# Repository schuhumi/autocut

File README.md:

autoCut
=======

autoCut is an automatic lawn mower robot. It features:
 - Four weel drive with kink steering
 - Motorized mowing height leveling
 - Two 85 watt mowing motors, each equipped with two very sharp blades, able to snap back on hard obstacles
 - On the fly interchangeable LiPo-battery with voltage monitoring
 - Wifi network connection for web interface which includes gamepad remote control
 - Raspberry Pi as its main computer and head of the microcontroller i2c-network

progress
========

What it can do already:
-----------------------
 - [drive system] works pretty much brilliant
 - [power supply] Measures individual cell voltages and rings an audible alarm in case of undervoltage or improper connected battery. Handles battery changes without losing power for the control system
 - [main module] Raspberry works quite well with ArchLinux ARM and provides a webinterface on the network. Will be replaced by Cubieboard 2 since RasPi has hardware I2C issues
 - [mowing module] Runs the mowing motors with a reasonably decent rpm regulation algorithm. Electrical mowing height adjustment through web interface is implemented.

What it can't do yet:
---------------------
 - [power supply] Measure the current as well as the total battery voltage
 - [general] No environmental sensoring for automatic movement yet, so manual control is needed

Things to improve:
------------------
 - [power supply] design a proper pcb (its on a prototyping board so far)
 - [mowing module] Change FETs for ones with lower heat dissipation and enhance the rpm regulation algorithm

Preserved for the future:
-------------------------
 - Build an automatic battery changing and charging station

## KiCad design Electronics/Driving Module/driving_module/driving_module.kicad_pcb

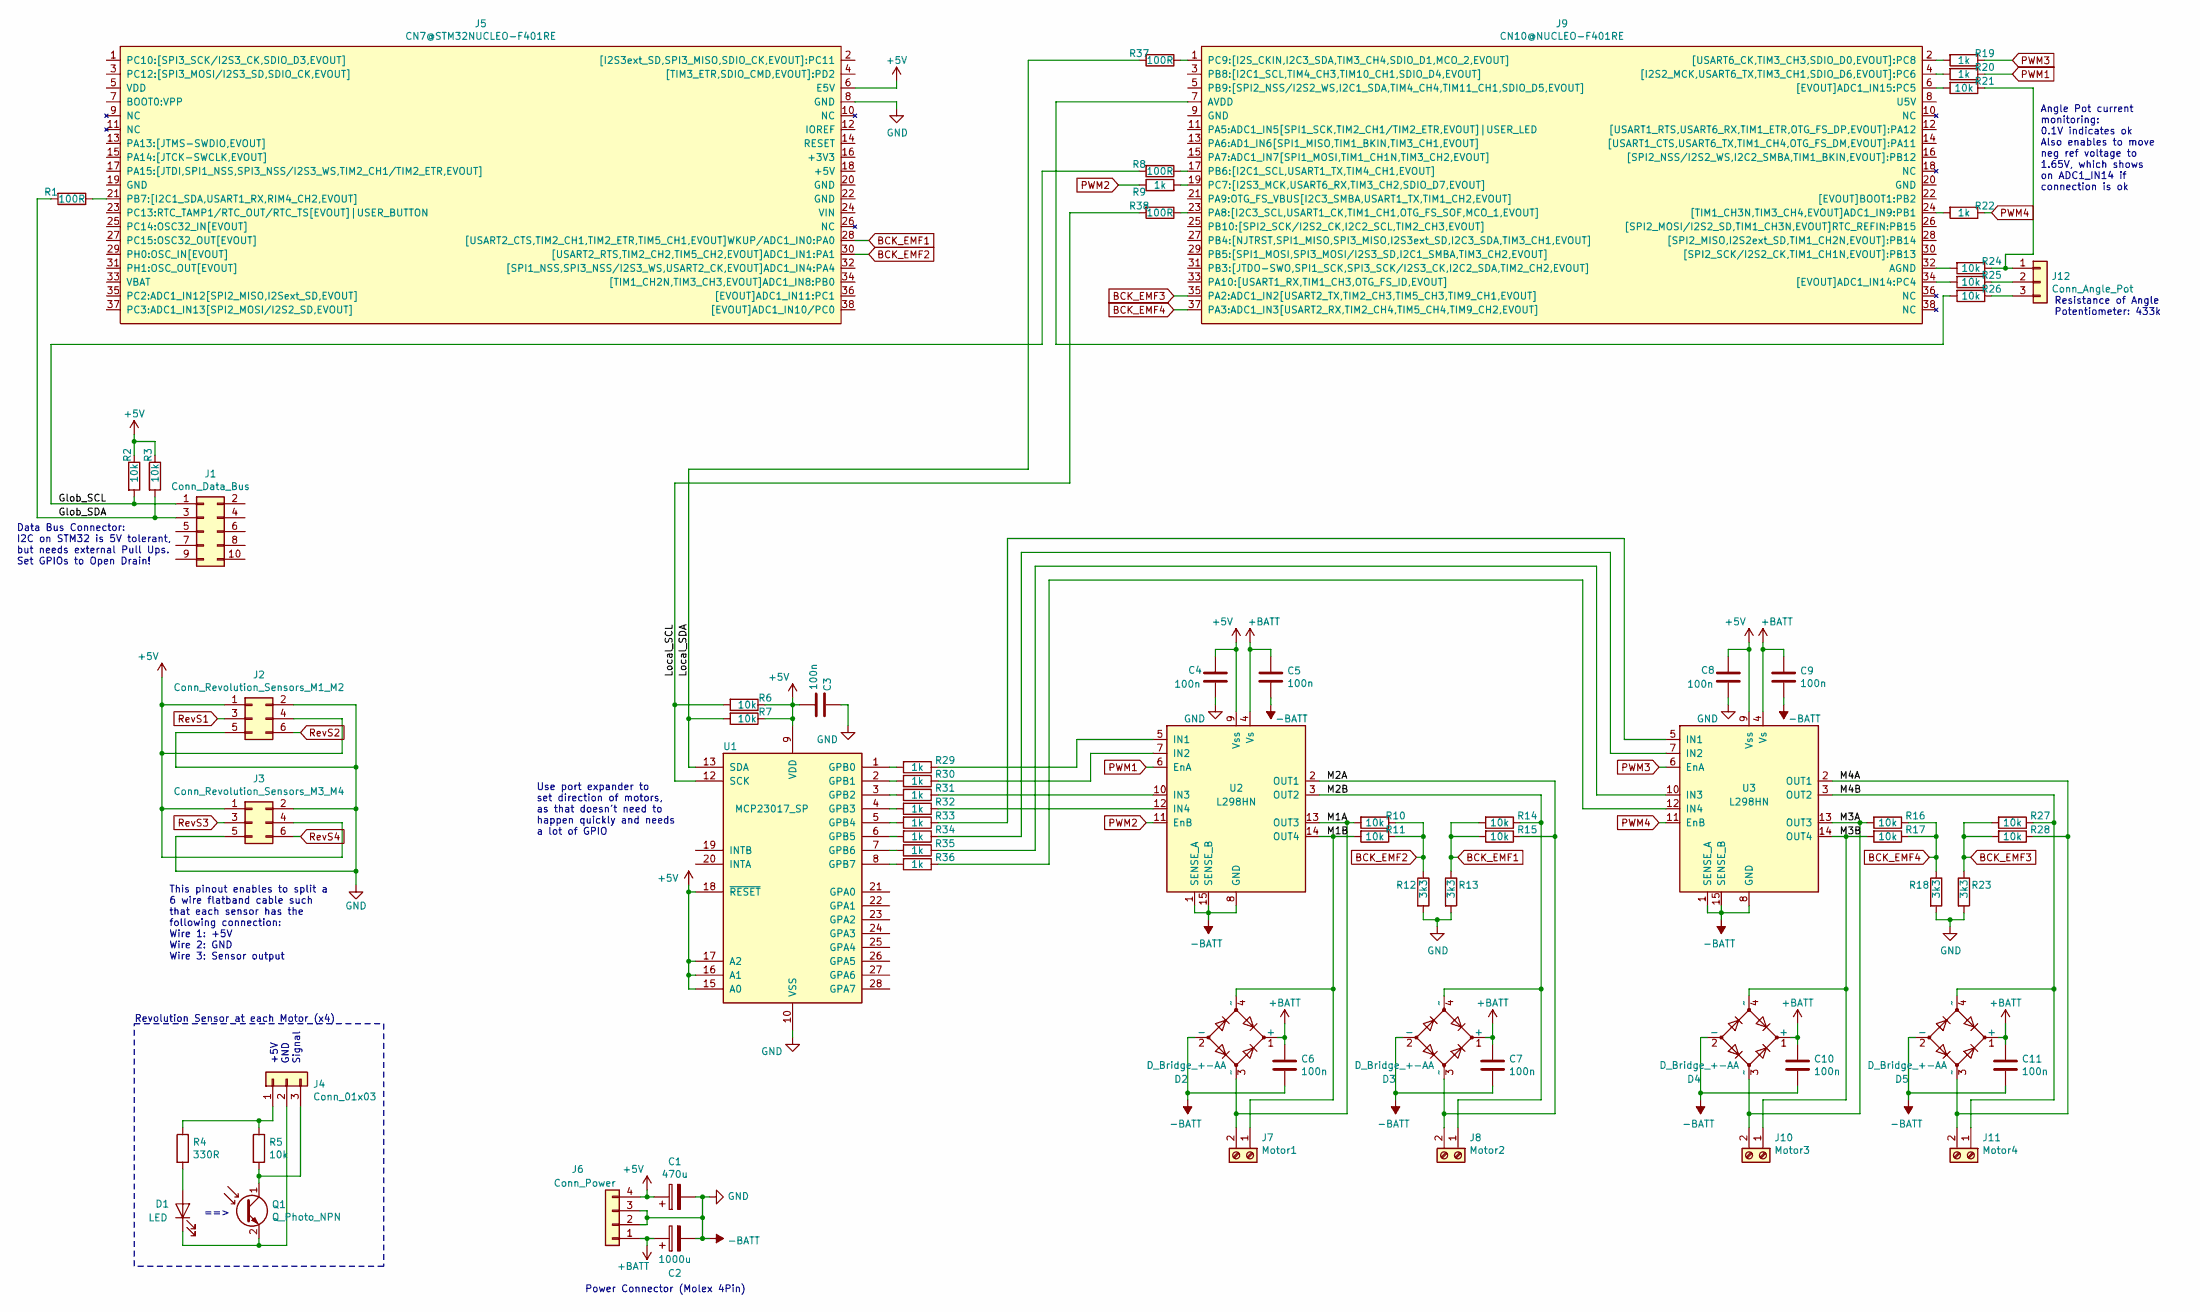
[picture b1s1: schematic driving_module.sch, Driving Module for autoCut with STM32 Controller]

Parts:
C1: 470u; CP_Radial_D8.0mm_P5.00mm
C2: 1000u; CP_Radial_D12.5mm_P5.00mm
C3, C4, C5, C6, C7, C8, C9, C10, C11: 100n; C_0805_2012Metric
D1: LED; LED_D3.0mm_Clear
D2, D3, D4, D5: D_Bridge_+-AA; Diode_Bridge_Diotec_SO-DIL-Slim
J1: Conn_Data_Bus; IDC-Header_2x05_P2.54mm_Vertical
J2: Conn_Revolution_Sensors_M1_M2; IDC-Header_2x03_P2.54mm_Vertical
J3: Conn_Revolution_Sensors_M3_M4; IDC-Header_2x03_P2.54mm_Vertical
J4: Conn_01x03; PinHeader_1x03_P2.54mm_Vertical
J5: CN7@STM32NUCLEO-F401RE; PinSocket_2x19_P2.54mm_Vertical
J6: Conn_Power; xess-MOLEX-8981-04P
J7: Motor1; TerminalBlock_bornier-2_P5.08mm
J8: Motor2; TerminalBlock_bornier-2_P5.08mm
J9: CN10@NUCLEO-F401RE; PinSocket_2x19_P2.54mm_Vertical
J10: Motor3; TerminalBlock_bornier-2_P5.08mm
J11: Motor4; TerminalBlock_bornier-2_P5.08mm
J12: Conn_Angle_Pot; PinHeader_1x03_P2.54mm_Vertical
Q1: Q_Photo_NPN; LED_D3.0mm_Clear
R1, R8, R37, R38: 100R; R_0805_2012Metric
R2, R3, R5, R6, R7, R10, R11, R14, R15, R16, R17, R21, R24, R25, R26, R27, R28: 10k; R_0805_2012Metric
R4: 330R; R_0805_2012Metric
R9, R19, R20, R22, R29, R30, R31, R32, R33, R34, R35, R36: 1k; R_0805_2012Metric
R12, R13, R18, R23: 3k3; R_Axial_DIN0207_L6.3mm_D2.5mm_P7.62mm_Horizontal
U1: MCP23017_SP; DIP-28_W7.62mm
U2, U3: L298HN; TO-220-15_P2.54x2.54mm_StaggerOdd_Lead4.58mm_Vertical_bent_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

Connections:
+5V: C1.1, C3.2, C4.1, C8.1, J2.1, J2.4, J3.1, J3.4, J5.6 (E5V), J6.4, R2.1, R3.1, R6.1, R7.1, U1.9 (VDD), U1.15 (A0), U1.16 (A1), U1.17 (A2), U1.18 (~RESET~), U2.9 (Vss), U3.9 (Vss)
+BATT: C2.1, C5.1, C6.1, C7.1, C9.1, C10.1, C11.1, D2.1 (+), D3.1 (+), D4.1 (+), D5.1 (+), J6.1, U2.4 (Vs), U3.4 (Vs)
-BATT: C1.2, C2.2, C3.1, C4.2, C5.2, C6.2, C7.2, C8.2, C9.2, C10.2, C11.2, D2.2 (-), D3.2 (-), D4.2 (-), D5.2 (-), J2.2, J2.5, J3.2, J3.5, J5.8 (GND), J6.2, J6.3, R12.2, R13.2, R18.2, R23.2, U1.10 (VSS), U2.1 (SENSE_A), U2.8 (GND), U2.15 (SENSE_B), U3.1 (SENSE_A), U3.8 (GND), U3.15 (SENSE_B)
/Glob_SCL: J1.1, R2.2, R8.2
/Glob_SDA: J1.3, R1.2, R3.2
/Local_SCL: R6.2, R38.2, U1.12 (SCK)
/Local_SDA: R7.2, R37.2, U1.13 (SDA)
/M1A: D2.3 (~~), J7.2, R10.2, U2.13 (OUT3)
/M1B: D2.4 (~~), J7.1, R11.2, U2.14 (OUT4)
/M2A: D3.3 (~~), J8.2, R15.1, U2.2 (OUT1)
/M2B: D3.4 (~~), J8.1, R14.1, U2.3 (OUT2)
/M3A: D4.3 (~~), J10.2, R16.2, U3.13 (OUT3)
/M3B: D4.4 (~~), J10.1, R17.2, U3.14 (OUT4)
/M4A: D5.3 (~~), J11.2, R28.1, U3.2 (OUT1)
/M4B: D5.4 (~~), J11.1, R27.1, U3.3 (OUT2)
BCK_EMF1: J5.28 ([USART2_CTS,TIM2_CH1,TIM2_ETR,TIM5_CH1,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), R13.1, R14.2, R15.2
BCK_EMF2: J5.30 ([USART2_RTS,TIM2_CH2,TIM5_CH2,EVOUT]ADC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), R10.1, R11.1, R12.1
BCK_EMF3: J9.35 (PA2:ADC1_IN2[USART2_TX,TIM2_CH3,TIM5_CH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), R23.1, R27.2, R28.2
BCK_EMF4: J9.37 (PA3:ADC1_IN3[USART2_RX,TIM2_CH4,TIM5_CH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), R16.1, R17.1, R18.1
unnamed: D1.1 (K), J4.2, Q1.2 (E)
unnamed: D1.2 (A), R4.2
unnamed: J4.1, R4.1, R5.1
unnamed: J4.3, Q1.1 (C), R5.2
unnamed: J5.21 (PB7:[I2C1_SDA,USART1_RX,RIM4_CH2,EVOUT]), R1.1
unnamed: J9.1 (PC9:[I2S_CKIN,I2C3_SDA,TIM3_CH4,SDIO_D1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), R37.1
unnamed: J9.2 ([USART6_CK,TIM3_CH3,SDIO_D0,EVOUT]:PC8), R19.2
unnamed: J9.4 ([I2S2_MCK,USART6_TX,TIM3_CH1,SDIO_D6,EV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), R20.2
unnamed: J9.6 ([EVOUT]ADC1_IN15:PC5), R21.2
unnamed: J9.7 (AVDD), R26.2
unnamed: J9.17 (PB6:[I2C1_SCL,USART1_TX,TIM4_CH1,EVOUT]), R8.1
unnamed: J9.19 (PC7:[I2S3_MCK,USART6_RX,TIM3_CH2,SDIO_D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), R9.2
unnamed: J9.23 (PA8:[I2C3_SCL,USART1_CK,TIM1_CH1,OTG_FS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), R38.1
unnamed: J9.24 ([TIM1_CH3N,TIM3_CH4,EVOUT]ADC1_IN9:PB1), R22.2
unnamed: J9.32 (AGND), R24.2
unnamed: J9.34 ([EVOUT]ADC1_IN14:PC4), R25.2
unnamed: J12.1, R21.1, R24.1
unnamed: J12.2, R25.1
unnamed: J12.3, R26.1
unnamed: R29.1, U2.5 (IN1)
unnamed: R29.2, U1.1 (GPB0)
unnamed: R30.1, U2.7 (IN2)
unnamed: R30.2, U1.2 (GPB1)
unnamed: R31.1, U2.10 (IN3)
unnamed: R31.2, U1.3 (GPB2)
unnamed: R32.1, U2.12 (IN4)
unnamed: R32.2, U1.4 (GPB3)
unnamed: R33.1, U3.5 (IN1)
unnamed: R33.2, U1.5 (GPB4)
unnamed: R34.1, U3.7 (IN2)
unnamed: R34.2, U1.6 (GPB5)
unnamed: R35.1, U3.10 (IN3)
unnamed: R35.2, U1.7 (GPB6)
unnamed: R36.1, U3.12 (IN4)
unnamed: R36.2, U1.8 (GPB7)
PWM1: R20.1, U2.6 (EnA)
PWM2: R9.1, U2.11 (EnB)
PWM3: R19.1, U3.6 (EnA)
PWM4: R22.1, U3.11 (EnB)
RevS1: J2.3
RevS2: J2.6
RevS3: J3.3
RevS4: J3.6

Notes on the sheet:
Resistance of Angle Potentiometer: 433k
Angle Pot current monitoring: 0.1V indicates ok Also enables to move neg ref voltage to 1.65V, which shows on ADC1_IN14 if connection is ok
Data Bus Connector: I2C on STM32 is 5V tolerant, but needs external Pull Ups. Set GPIOs to Open Drain!
Use port expander to set direction of motors, as that doesn't need to happen quickly and needs a lot of GPIO
This pinout enables to split a 6 wire flatband cable such that each sensor has the following connection: Wire 1: +5V Wire 2: GND Wire 3: Sensor output
+5V GND Signal
==>
Revolution Sensor at each Motor (x4)
Power Connector (Molex 4Pin)

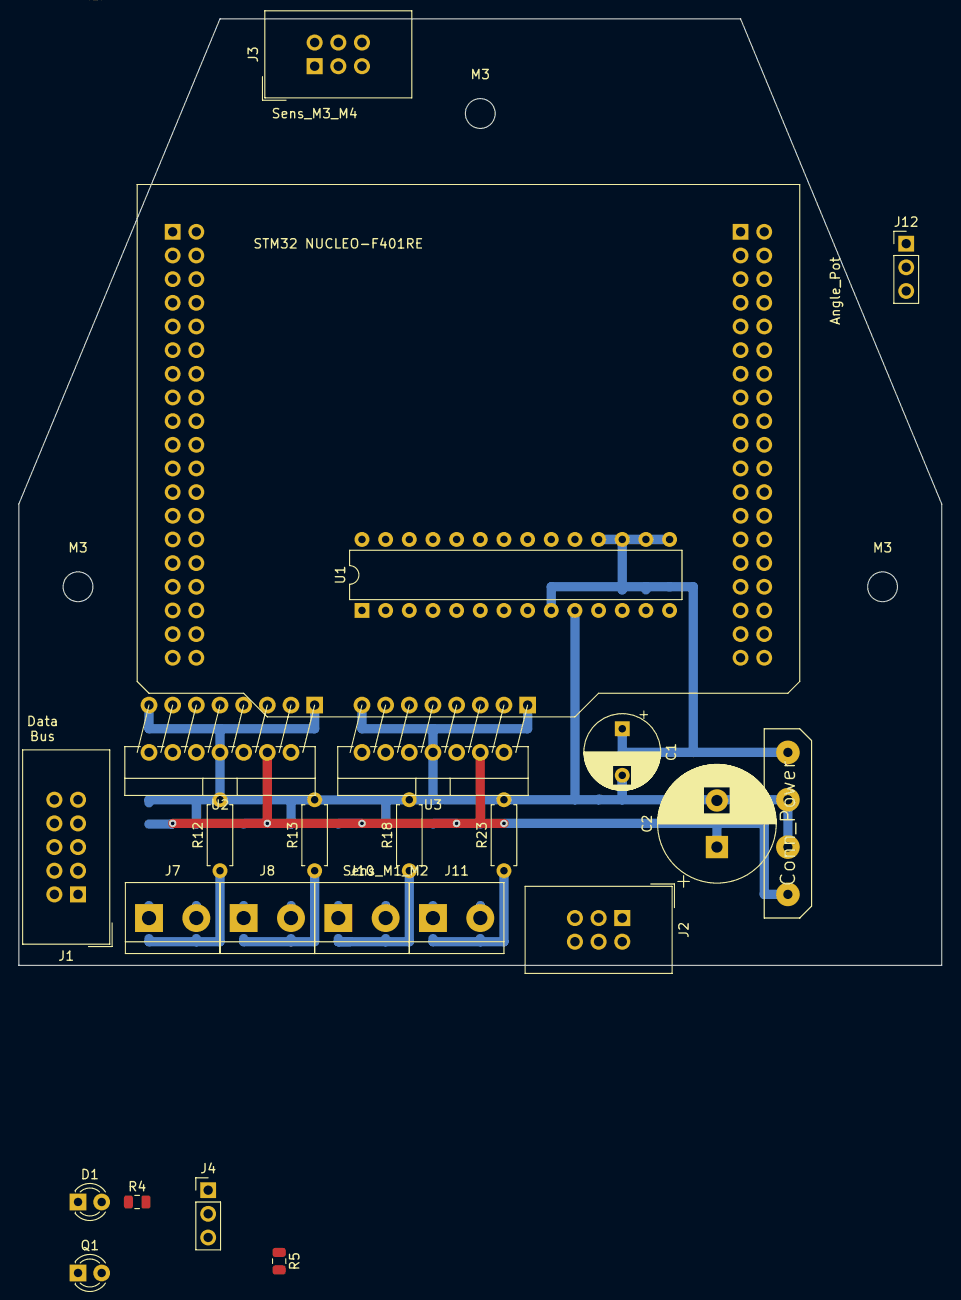
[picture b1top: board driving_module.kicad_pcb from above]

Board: 4 copper layers, 99.1 x 101.6 mm, 73 parts (0 on the bottom side), 58 nets.

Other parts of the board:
M3, M3#2, M3#3: MountingHole_3.2mm_M3

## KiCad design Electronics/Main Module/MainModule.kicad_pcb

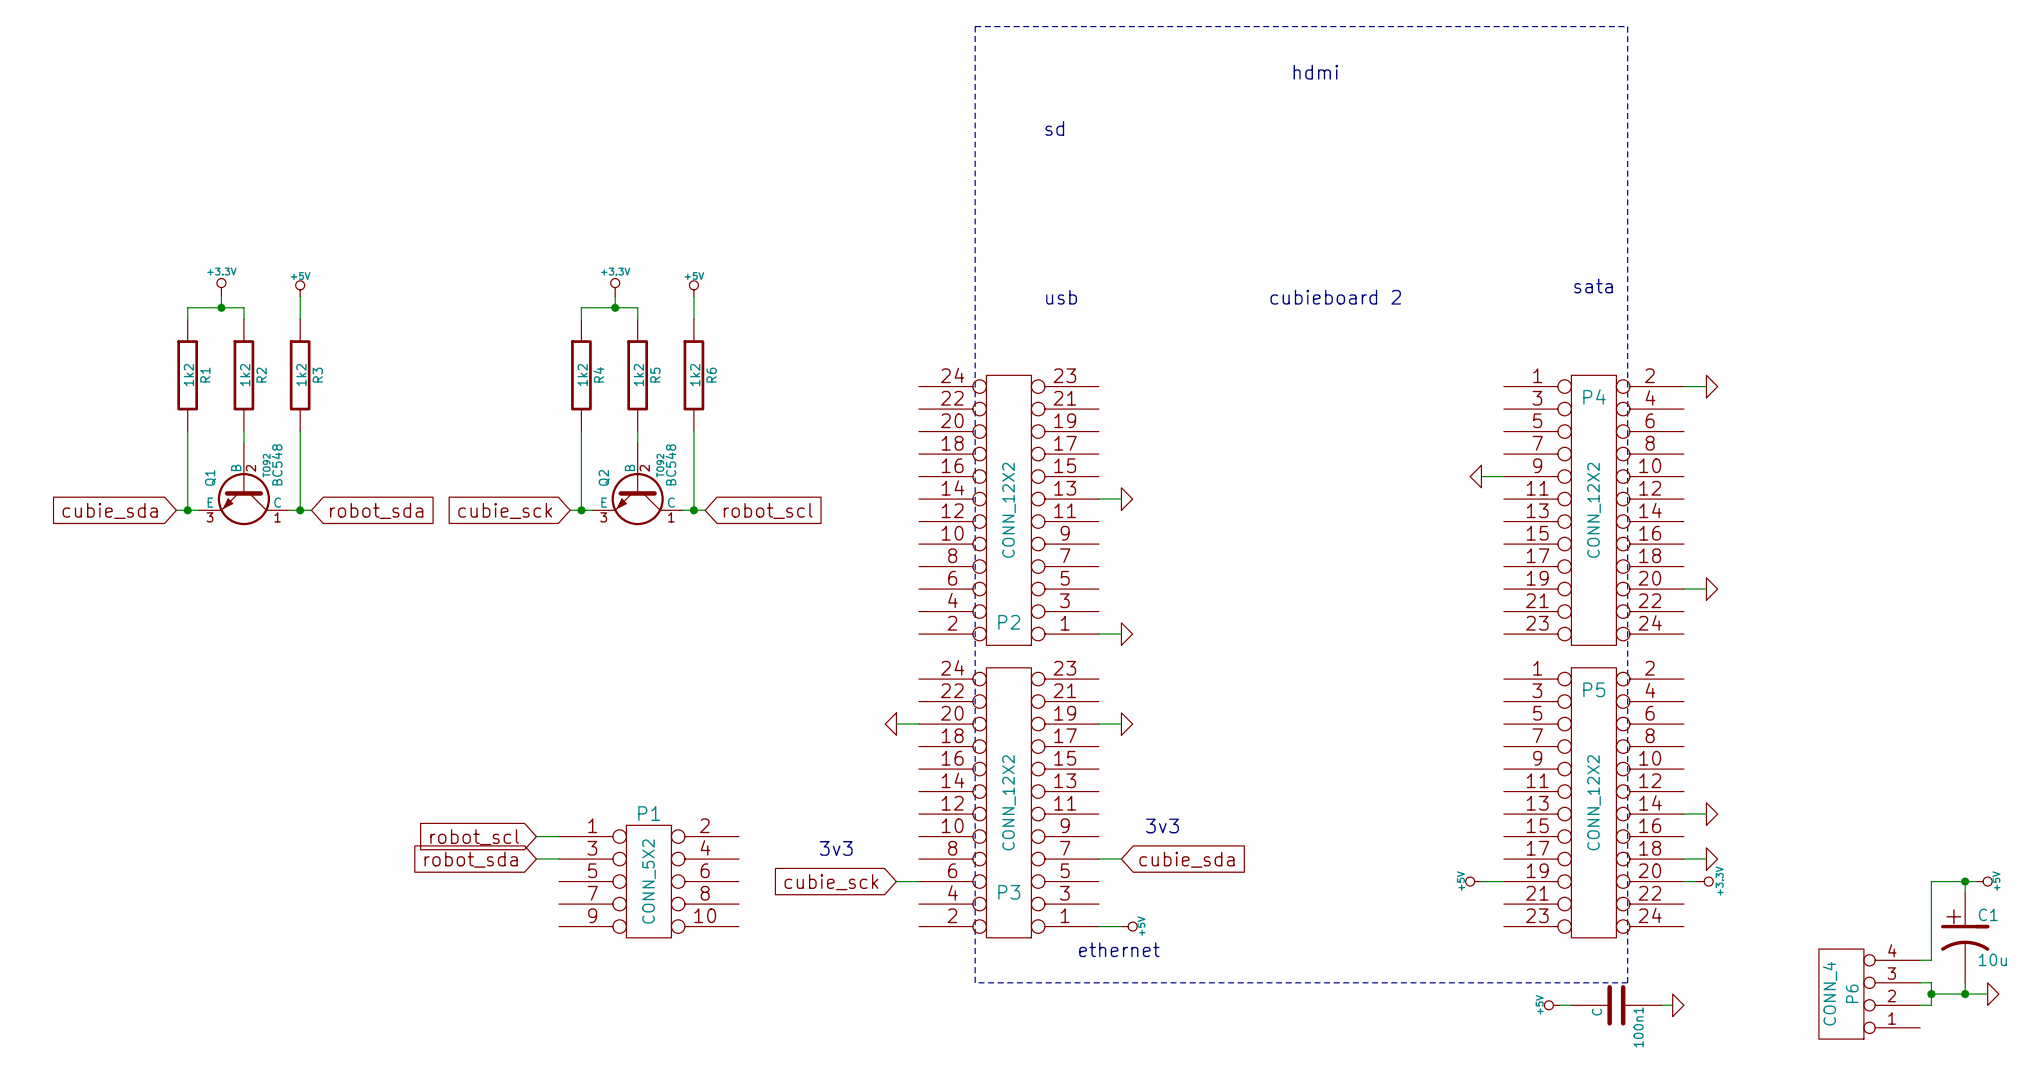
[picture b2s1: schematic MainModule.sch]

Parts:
100n1: C; SMD-0805
C1: 10u; Elko_vert_DM5_RM2-5
P1: CONN_5X2; VASCH5x2
P2, P3, P4, P5: CONN_12X2; SMD2mm_Header_12x2
P6: CONN_4; Molex
Q1, Q2: BC548; TO92
R1, R2, R3, R4, R5, R6: 1k2; R_0805

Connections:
+3.3V: P5.20, R1.1, R2.1, R4.1, R5.1
+5V: 100n1.2, C1.1, P3.1, P5.19, P6.4, R3.1, R6.1
GND: 100n1.1, C1.2, P2.1, P2.13, P3.19, P3.20, P4.2, P4.9, P4.20, P5.14, P5.18, P6.2, P6.3
unnamed: Q1.2 (B), R2.2
unnamed: Q2.2 (B), R5.2
cubie_sck: P3.6, Q2.3 (E), R4.2
cubie_sda: P3.7, Q1.3 (E), R1.2
robot_scl: P1.1, Q2.1 (C), R6.2
robot_sda: P1.3, Q1.1 (C), R3.2

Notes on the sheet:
cubieboard 2
sata
ethernet
usb
hdmi
3v3

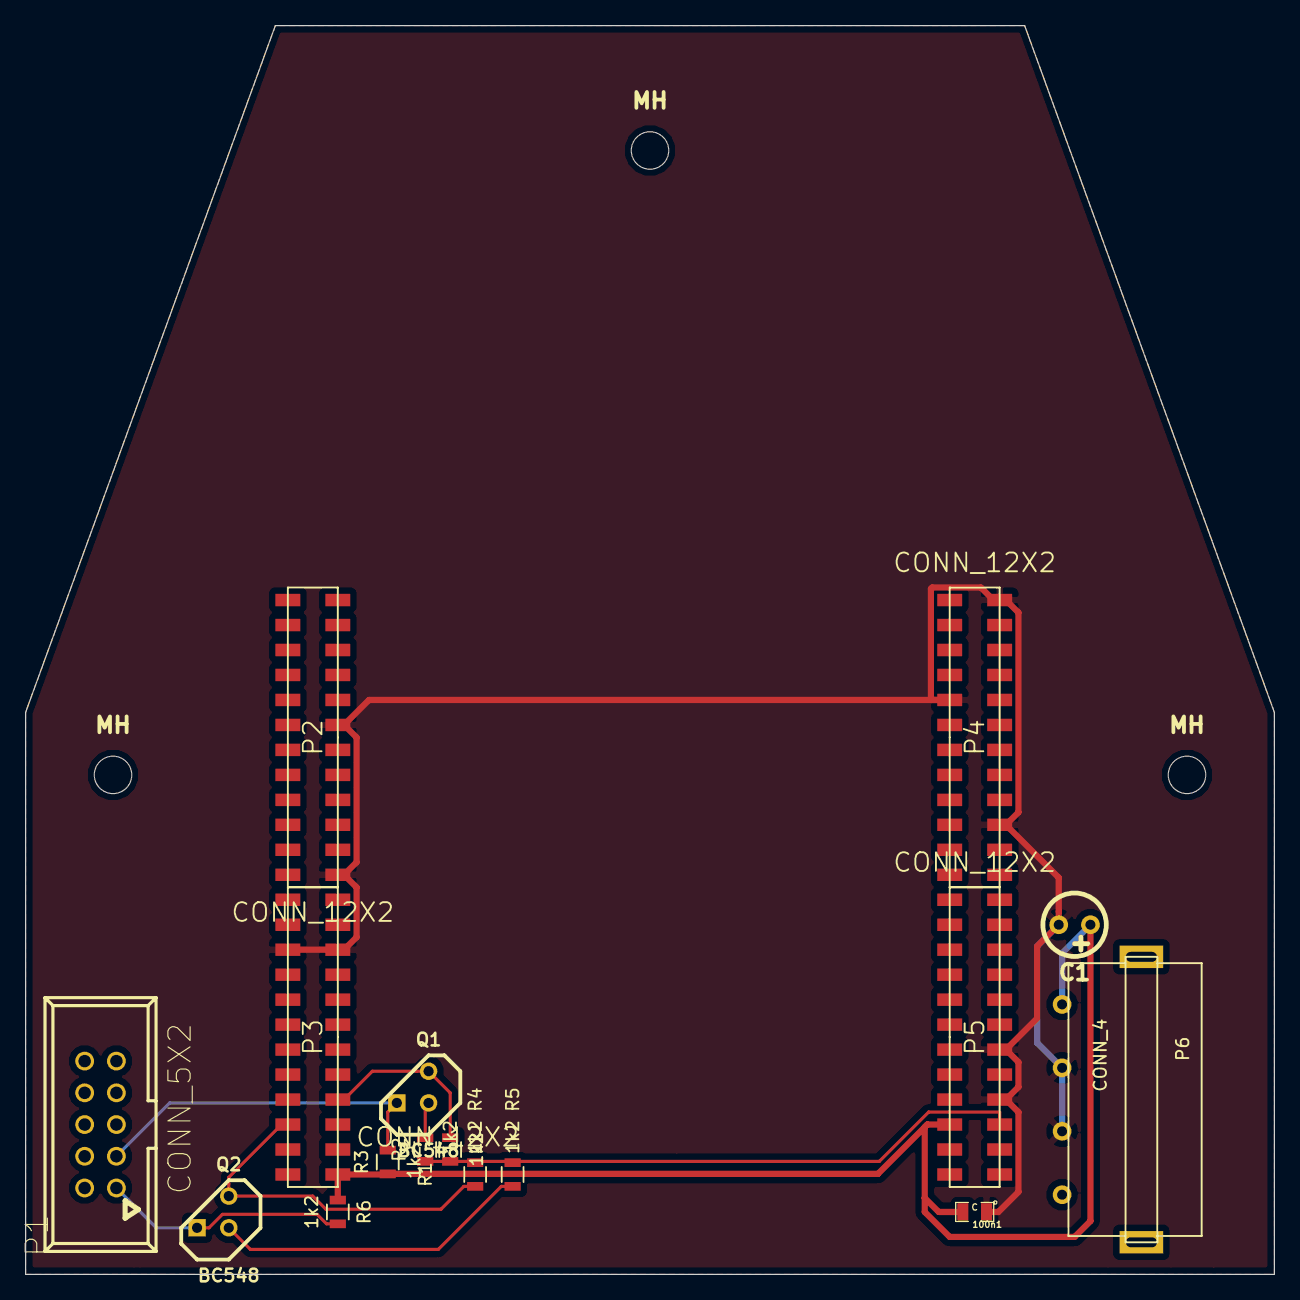
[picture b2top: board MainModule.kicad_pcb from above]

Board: 2 copper layers, 100.0 x 100.0 mm, 19 parts (0 on the bottom side), 9 nets.

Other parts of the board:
MH: MountingHole_3mm_RevA_Date21Jun2010; MountingHole_3mm
MH#2, MH#3: MountingHole_3mm_RevA_Date21Jun2010; MountingHole_3mm

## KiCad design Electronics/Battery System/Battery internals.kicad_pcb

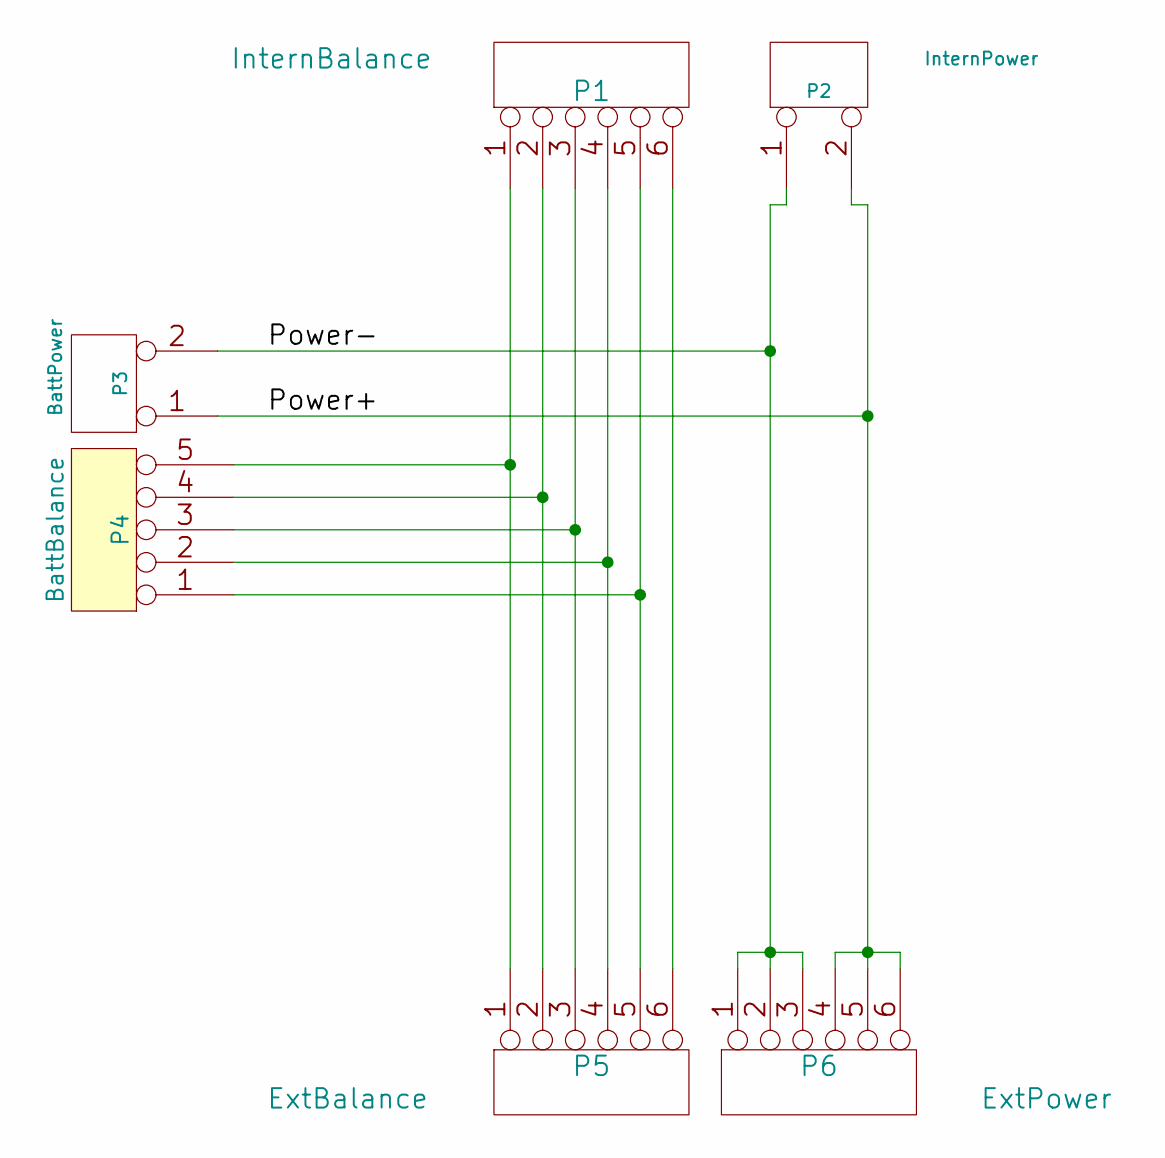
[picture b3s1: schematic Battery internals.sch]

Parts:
P1: InternBalance; Socket_Strip_Straight_1x06
P2: InternPower; PowerConnect_Handsolder
P3: BattPower; PowerConnect_Handsolder
P4: BattBalance; Pin_Header_Straight_1x05
P5: ExtBalance; Connector_MPX_6Pin
P6: ExtPower; Connector_MPX_6Pin

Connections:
/Power+: P2.2 (PM), P3.1, P6.4, P6.5, P6.6
/Power-: P2.1, P3.2 (PM), P6.1, P6.2, P6.3
unnamed: P1.1, P4.5, P5.1
unnamed: P1.2, P4.4, P5.2
unnamed: P1.3, P4.3, P5.3
unnamed: P1.4, P4.2, P5.4
unnamed: P1.5, P4.1, P5.5
unnamed: P1.6, P5.6

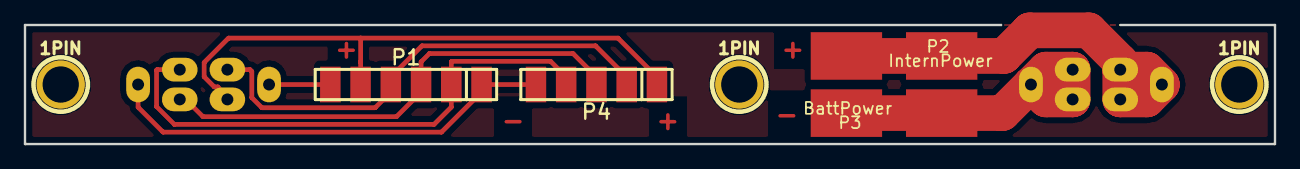
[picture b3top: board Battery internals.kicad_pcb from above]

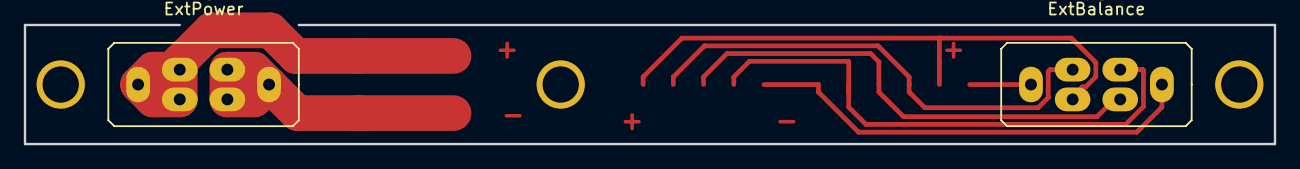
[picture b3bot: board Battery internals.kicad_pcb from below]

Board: 2 copper layers, 105.0 x 10.0 mm, 9 parts (2 on the bottom side), 8 nets.

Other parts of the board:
1PIN, 1PIN#2, 1PIN#3: P***; 1pin

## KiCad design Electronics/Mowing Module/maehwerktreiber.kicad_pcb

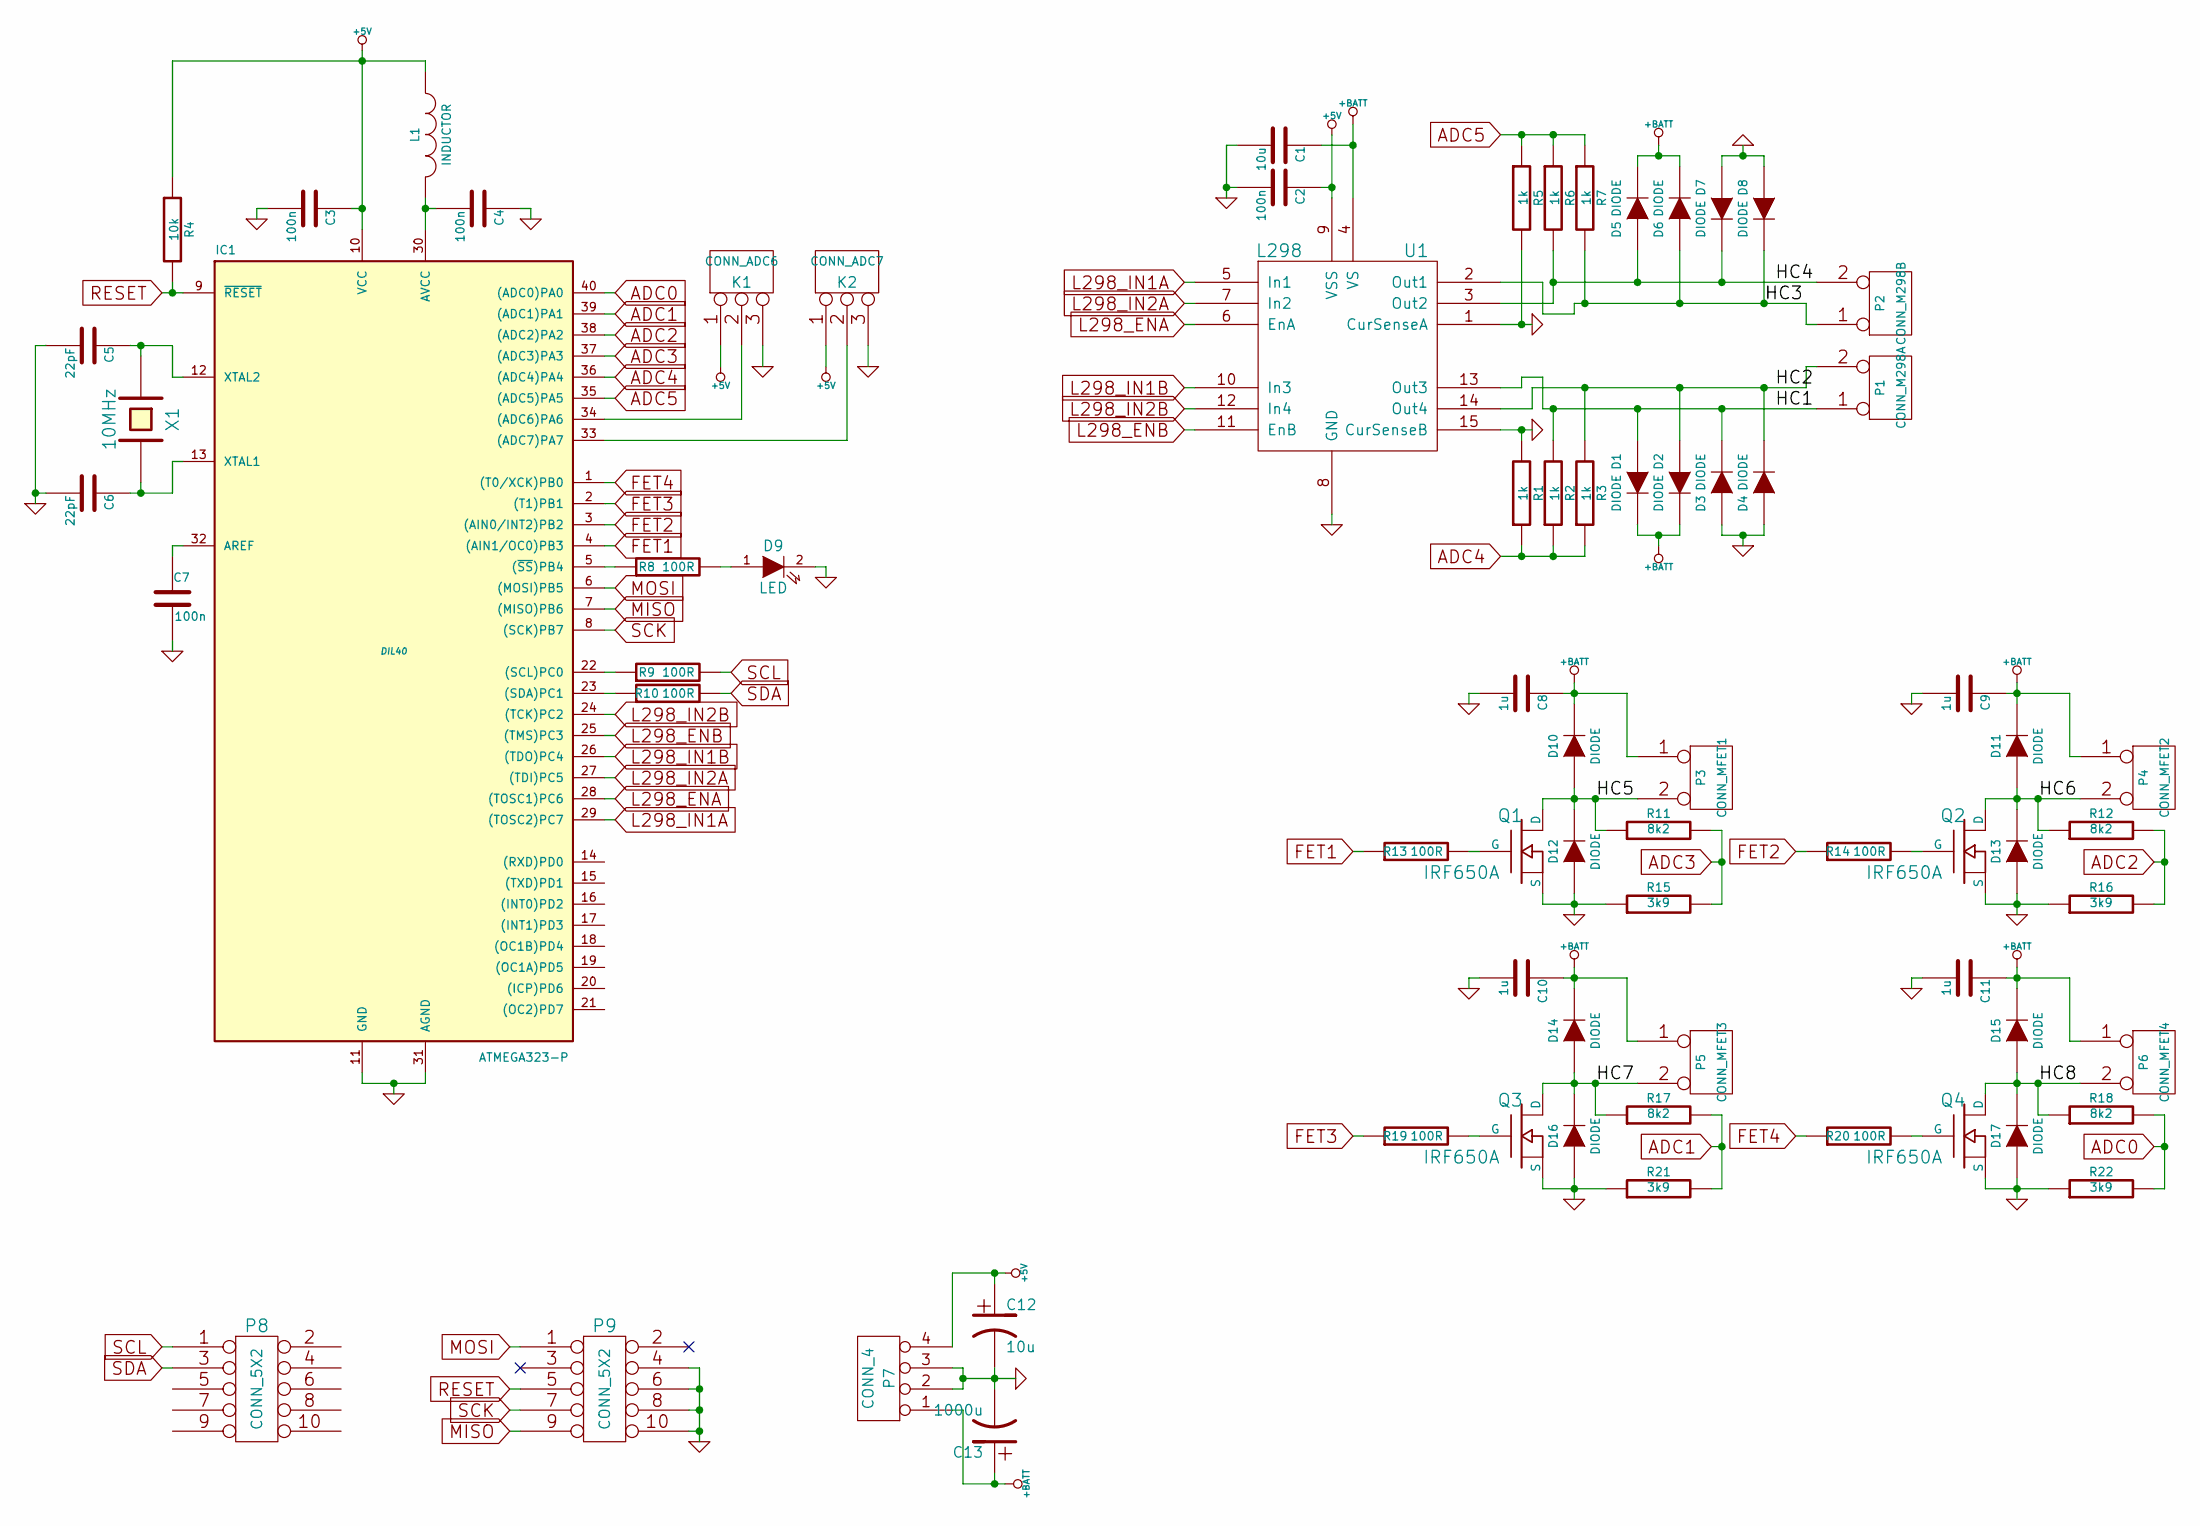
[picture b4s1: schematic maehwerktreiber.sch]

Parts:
C1, C12: 10u
C2, C3, C4, C7: 100n
C5, C6: 22pF
C8, C9, C10, C11: 1u
C13: 1000u
D1, D2, D3, D4, D5, D6, D7, D8, D10, D11, D12, D13, D14, D15, D16, D17: DIODE
D9: LED
IC1: ATMEGA323-P; DIL40
K1: CONN_ADC6
K2: CONN_ADC7
L1: INDUCTOR
P1: CONN_M298A
P2: CONN_M298B
P3: CONN_MFET1
P4: CONN_MFET2
P5: CONN_MFET3
P6: CONN_MFET4
P7: CONN_4
P8, P9: CONN_5X2
Q1, Q2, Q3, Q4: IRF650A
R1, R2, R3, R5, R6, R7: 1k
R4: 10k
R8, R9, R10, R13, R14, R19, R20: 100R
R11, R12, R17, R18: 8k2
R15, R16, R21, R22: 3k9
U1: L298
X1: 10MHz

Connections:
+5V: C2.1, C3.1, C12.1, IC1.10 (VCC), K1.1, K2.1, L1.1, P7.4, R4.1, U1.9 (VSS)
+BATT: C1.1, C8.1, C9.1, C10.1, C11.1, C13.1, D1.2 (K), D2.2 (K), D5.2 (K), D6.2 (K), D10.2 (K), D11.2 (K), D14.2 (K), D15.2 (K), P3.1, P4.1, P5.1, P6.1, P7.1, U1.4 (VS)
/HC1: D1.1 (A), D3.2 (K), P1.1, R2.2, U1.13 (Out3)
/HC2: D2.1 (A), D4.2 (K), P1.2 (PM), R3.2, U1.14 (Out4)
/HC3: D6.1 (A), D8.2 (K), P2.1, R7.2, U1.2 (Out1)
/HC4: D5.1 (A), D7.2 (K), P2.2 (PM), R6.2, U1.3 (Out2)
/HC5: D10.1 (A), D12.2 (K), P3.2 (PM), Q1.2 (D), R11.1
/HC6: D11.1 (A), D13.2 (K), P4.2 (PM), Q2.2 (D), R12.1
/HC7: D14.1 (A), D16.2 (K), P5.2 (PM), Q3.2 (D), R17.1
/HC8: D15.1 (A), D17.2 (K), P6.2 (PM), Q4.2 (D), R18.1
ADC0: IC1.40 ((ADC0)PA0), R18.2, R22.2
ADC1: IC1.39 ((ADC1)PA1), R17.2, R21.2
ADC2: IC1.38 ((ADC2)PA2), R12.2, R16.2
ADC3: IC1.37 ((ADC3)PA3), R11.2, R15.2
ADC4: IC1.36 ((ADC4)PA4), R1.1, R2.1, R3.1
ADC5: IC1.35 ((ADC5)PA5), R5.1, R6.1, R7.1
FET1: IC1.4 ((AIN1/OC0)PB3), R13.1
FET2: IC1.3 ((AIN0/INT2)PB2), R14.1
FET3: IC1.2 ((T1)PB1), R19.1
FET4: IC1.1 ((T0/XCK)PB0), R20.1
GND: C1.2, C2.2, C3.2, C4.1, C5.2, C6.2, C7.2, C8.2, C9.2, C10.2, C11.2, C12.2, C13.2, D3.1 (A), D4.1 (A), D7.1 (A), D8.1 (A), D9.2 (K), D12.1 (A), D13.1 (A), D16.1 (A), D17.1 (A), IC1.11 (GND), IC1.31 (AGND), K1.3, K2.3, P7.2, P7.3, P9.4, P9.6, P9.8, P9.10, Q1.3 (S), Q2.3 (S), Q3.3 (S), Q4.3 (S), R1.2, R5.2, R15.1, R16.1, R21.1, R22.1, U1.1 (CurSenseA), U1.8 (GND), U1.15 (CurSenseB)
L298_ENA: IC1.28 ((TOSC1)PC6), U1.6 (EnA)
L298_ENB: IC1.25 ((TMS)PC3), U1.11 (EnB)
L298_IN1A: IC1.29 ((TOSC2)PC7), U1.5 (In1)
L298_IN1B: IC1.26 ((TDO)PC4), U1.10 (In3)
L298_IN2A: IC1.27 ((TDI)PC5), U1.7 (In2)
L298_IN2B: IC1.24 ((TCK)PC2), U1.12 (In4)
MISO: IC1.7 ((MISO)PB6), P9.9
MOSI: IC1.6 ((MOSI)PB5), P9.1
unnamed: IC1.22 ((SCL)PC0), R9.1
unnamed: IC1.23 ((SDA)PC1), R10.1
unnamed: Q4.1 (G), R20.2
unnamed: Q3.1 (G), R19.2
unnamed: Q2.1 (G), R14.2
unnamed: D9.1 (A), R8.2
unnamed: IC1.5 ((~SS~)PB4), R8.1
unnamed: Q1.1 (G), R13.2
unnamed: IC1.33 ((ADC7)PA7), K2.2 (PM)
unnamed: IC1.34 ((ADC6)PA6), K1.2 (PM)
unnamed: C4.2, IC1.30 (AVCC), L1.2
unnamed: C7.1, IC1.32 (AREF)
unnamed: C5.1, IC1.12 (XTAL2), X1.1
unnamed: C6.1, IC1.13 (XTAL1), X1.2
RESET: IC1.9 (~RESET), P9.5, R4.2
SCK: IC1.8 ((SCK)PB7), P9.7
SCL: P8.1, R9.2
SDA: P8.3, R10.2

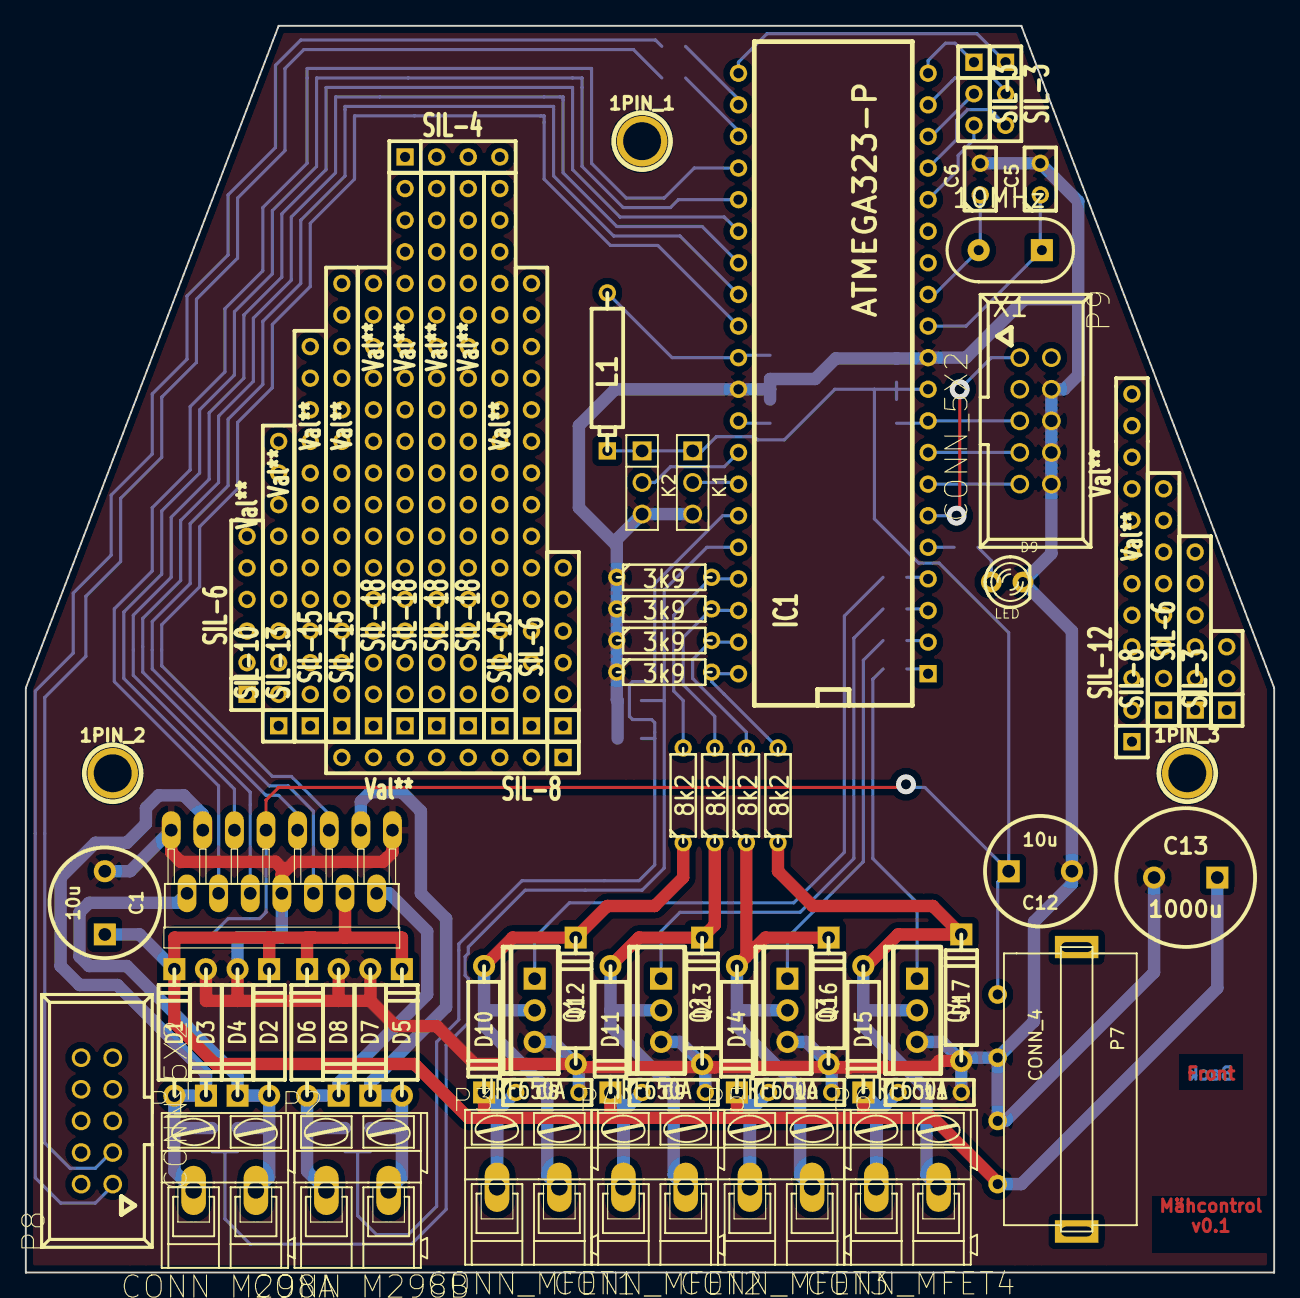
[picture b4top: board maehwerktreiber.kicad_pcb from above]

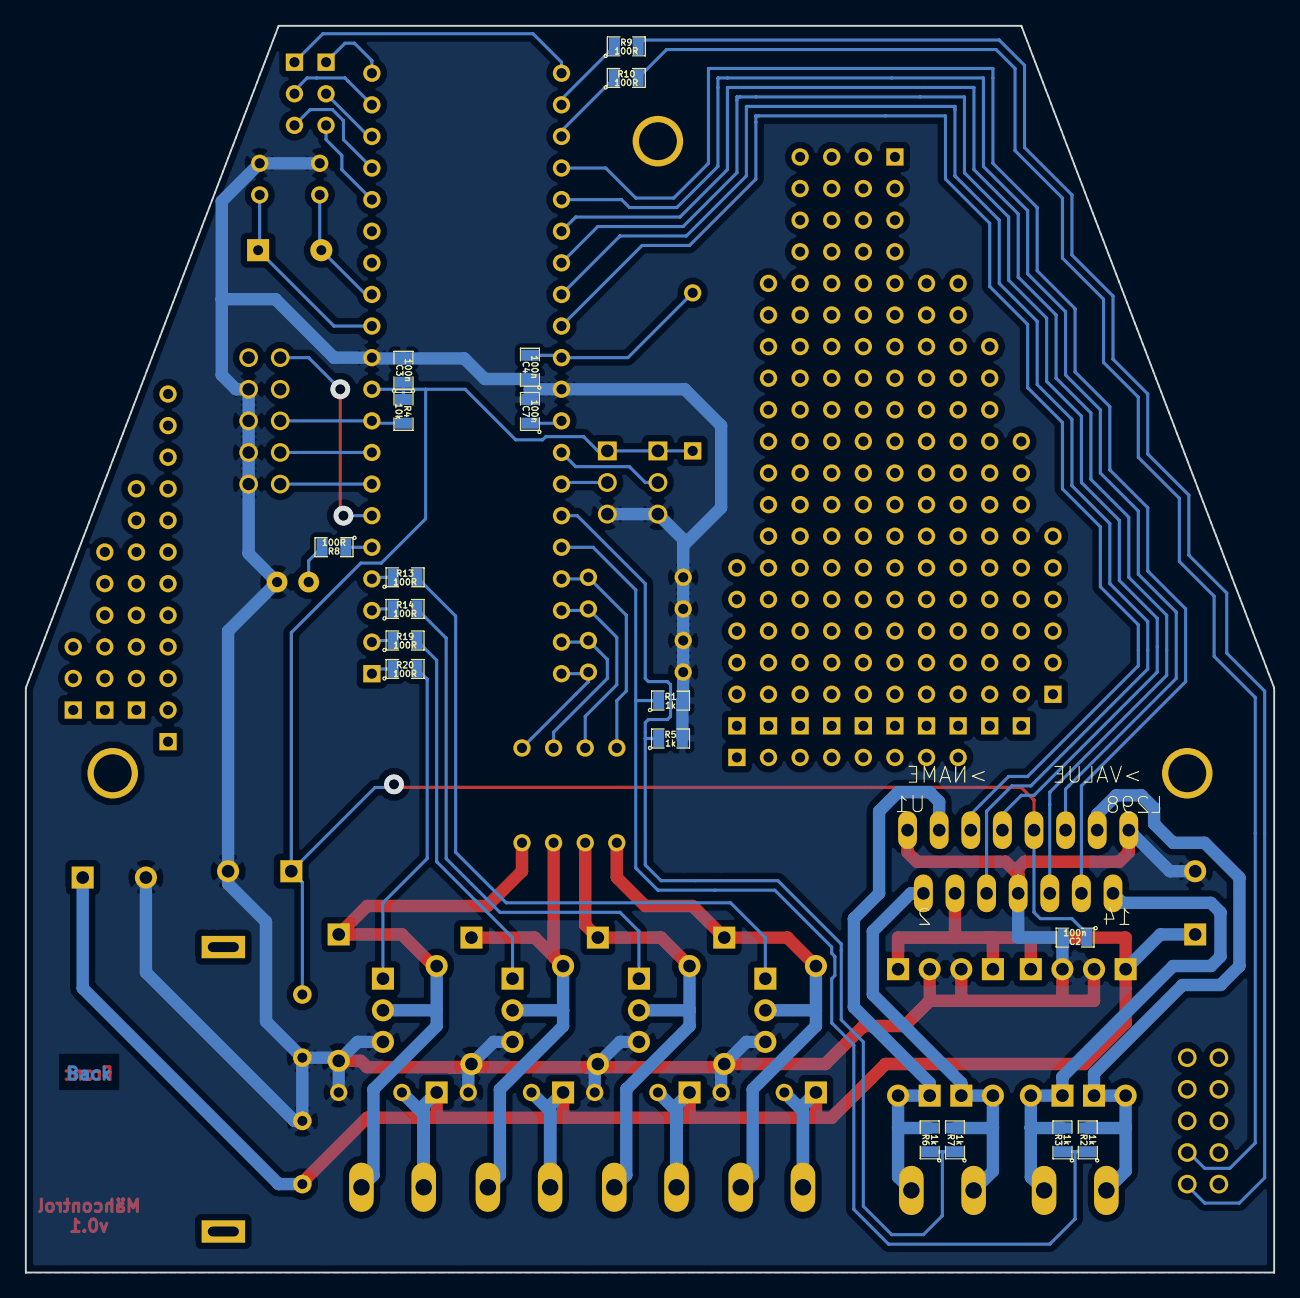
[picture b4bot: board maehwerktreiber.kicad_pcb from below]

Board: 2 copper layers, 100.3 x 100.2 mm, 93 parts (18 on the bottom side), 47 nets.

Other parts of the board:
1PIN_1: Hole1; 1pin
1PIN_2: Hole2; 1pin
1PIN_3: Hole3; 1pin
SIL-3, SIL-3#2, SIL-3#3: Val**; SIL-3
SIL-4: Val**; SIL-4
SIL-6, SIL-6#2, SIL-6#3: Val**; SIL-6
SIL-8, SIL-8#2: Val**; SIL-8
SIL-10: Val**; SIL-10
SIL-12: Val**; SIL-12
SIL-13: Val**; SIL-13
SIL-15, SIL-15#2, SIL-15#3: Val**; SIL-15
SIL-18, SIL-18#2, SIL-18#3, SIL-18#4: Val**; SIL-18
